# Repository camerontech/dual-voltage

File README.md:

5v & 3.3v Dual Voltage Regulator
================================
This board accepts a reasonable input (20v or less) and provides both 5v and 3.3v regulated outputs.

Parts
-----
Here's the parts I use when building this myself:

**10uF Capacitors**: [DigiKey Part P975-ND](http://www.digikey.com/product-search/en/capacitors/aluminum-capacitors/131081?k=P975-ND)

**0.1uF Capacitors**: [DigiKey Part 399-4266-ND](http://www.digikey.com/product-detail/en/C320C104M5U5TA/399-4266-ND/818042)

**5v Linear Regulator**: [DigiKey Part MC7805CT-BPMS-ND](http://www.digikey.com/product-detail/en/MC7805CT-BP/MC7805CT-BPMS-ND/804682)

**3.3v Linear Regulator**: [DigiKey Part 296-21633-5-ND](http://www.digikey.com/product-detail/en/UA78M33CKCS/296-21633-5-ND/1494026)

With these regulators you can run about 1.5A through the 5v output and 0.5A through the 3.3v output.
If you go that high you should seriously think about adding 
[heat sinks](http://www.digikey.com/product-search/en/fans-thermal-management/thermal-heat-sinks/1179752) 
to the regulators. To figure out how much power you're going to turn into heat, check this out: https://www.sparkfun.com/tutorials/217

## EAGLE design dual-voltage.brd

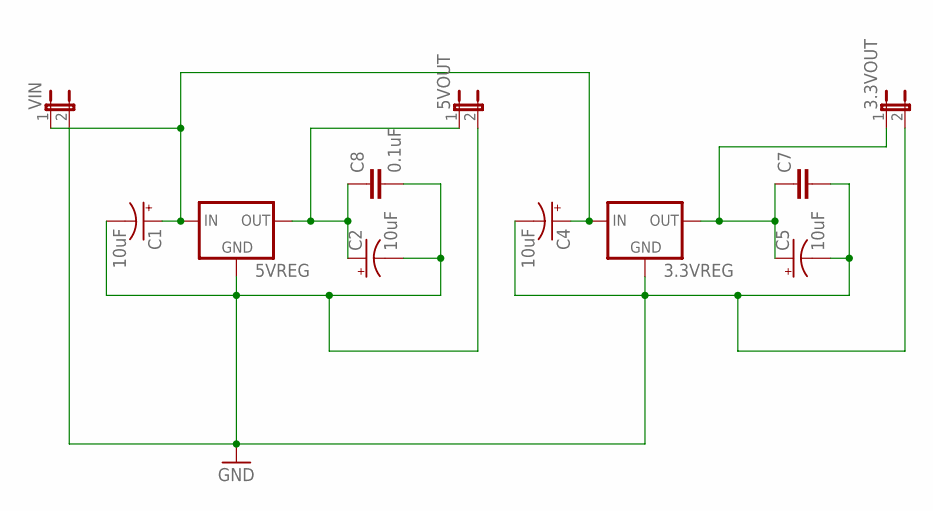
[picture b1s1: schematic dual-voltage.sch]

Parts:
3.3VOUT, 5VOUT: JUMPER-2PTH; 1X02
3.3VREG, 5VREG: 78XXS
C1, C2, C4, C5: 10uF; CPOL-RADIAL-10UF-25V
C7: CAPPTH2; CAP-PTH-SMALL2
C8: 0.1uF; CAP-PTH-SMALL2
VIN: JUMPER-2PTH; 1X02

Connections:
3.3V: 3.3VOUT.1, 3.3VREG.OUT, C5.1 (+), C7.1
5V: 5VOUT.1, 5VREG.OUT, C2.1 (+), C8.1
GND: 3.3VOUT.2, 3.3VREG.GND, 5VOUT.2, 5VREG.GND, C1.2 (-), C2.2 (-), C4.2 (-), C5.2 (-), C7.2, C8.2, VIN.2
unnamed: 3.3VREG.IN, 5VREG.IN, C1.1 (+), C4.1 (+), VIN.1

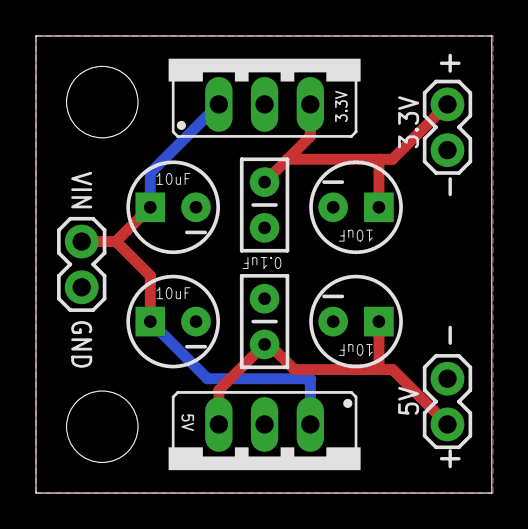
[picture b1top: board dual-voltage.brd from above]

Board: 2 copper layers, 25.3 x 25.4 mm, 11 parts (0 on the bottom side), 4 nets.

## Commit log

2013-09-19 Adds VERSION file
2013-09-19 Create gh-pages branch via GitHub
2013-09-19 Adds parts list
2013-09-19 Trace updates for new 3.3v regulator
2013-09-20 Updates voltage in/out jumpers to SparkFun components, updates 0.1uF capacitor footprint to SparkFun, bumps version to 1.1.0
2013-09-25 Set silkscreen labels to 15%
2013-10-01 Shrink screw holes to 5/32, bump to 1.1.1
2013-10-03 Create LICENSE
2013-10-04 Create CNAME
2013-10-20 Adds some images
2013-10-20 Set widths on images
2013-10-20 Adds links to bigger images
2013-10-20 Adds remaining images
2013-10-20 New images
2013-10-20 Adds images

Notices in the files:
parts and their libraries:
SparkFun-Capacitors: Licensing: CC v3.0 Share-Alike You are welcome to use this library for commercial purposes.
